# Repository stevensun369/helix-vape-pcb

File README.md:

# Helix Vape — Power Board

KiCad hardware design for the **Helix** temperature-control vape mod: a single-cell, USB-C powered board capable of delivering **1.0–10 V at up to 80 W** into a heating coil, with closed-loop current/voltage sensing and an ESP32-C6 running the [Helix-FW](https://github.com/stevensun369/helix-vape-fw) firmware.

The power stage is based on TI's **PMP20410** reference design, re-implemented and integrated with the MCU, sensing, and user-interface circuitry on a single board.

## Renders

| Front | Back |
|-------|------|
|  |  |

## Schematics

| Power & analog front-end | MCU & digital |
|--------------------------|---------------|
|  |  |

> Click either schematic to open the full-size SVG.

## How It Works

The board is a **digitally-controlled buck-boost regulator**. The MCU sets a target output via a DAC that injects into the regulator's feedback node, the ADC measures the actual coil current and voltage, and the firmware closes the loop with a PID controller. Because the regulator both bucks and boosts, it can hold a precise output regardless of where the battery sits in its discharge curve.

```
USB-C / Battery ──► LM5175 Buck-Boost ──► Q1–Q4 Power FETs ──► Coil
                         ▲                        │
                    MCP4726 DAC          RS1 / Rshunt sense
                         │                        │
                    ESP32-C6 ◄──────── ADS1015 ADC
```

## Key Components

| Ref | Part | Function |
|-----|------|----------|
| U1 | **LM5175PWP** | 4-switch synchronous buck-boost controller — the main 80 W power stage |
| U5 | **ESP32-C6-MINI-1U** | RISC-V MCU + Wi-Fi/BLE module; runs the control loop, UI, and safety logic |
| U4 | **ADS1015IDGS** | 12-bit I²C ADC — differential coil-current sensing plus single-ended Vout/Vbat |
| U3 | **MCP4726** | 12-bit I²C DAC — injects into the LM5175 feedback node to set output (inverse scaling) |
| Q1–Q4 | **BSC010NE2LSI** | 25 V, ~1 mΩ power MOSFETs — the buck-boost switching bridge |
| U2 | **LMR62014XMF** | Boost regulator for the auxiliary/gate-drive rail |
| U6 | **LP3986-30B3F** | 3.0 V LDO — clean rail for the MCU and analog parts |
| U8 | **USBLC6-2SC6** | USB-C data-line ESD / TVS protection |
| J1 | **USB-C Receptacle (16P)** | Charging and power input |
| RS1 / Rshunt1 | **2 mΩ / 10 mΩ shunts** | High-side and coil current sensing |
| L1 | **680 nH, 23 A** | Main power inductor (Chilisin) |
| BT1 | **1042 cell** | Battery connection |
| SW1 / SW2 | Push buttons | User input |

Full bill of materials with LCSC part numbers is in [`PRODUCTION_FILES/BOM-helix_vape.csv`](PRODUCTION_FILES/BOM-helix_vape.csv).

## Design Notes

- **Inverse DAC feedback:** higher DAC voltage produces *lower* output, so any logical fault or DAC reset biases the regulator toward a safe low-power idle (~1.0 V) rather than full power.
- **Shared I²C bus @ 400 kHz** ties together the ADC and DAC; the firmware arbitrates access to keep latency predictable under contention.
- **Differential current sensing** through the ADS1015 gives the firmware accurate, real-time coil current for PID power control and over-current safety.

## Files

| Path | Contents |
|------|----------|
| `helix_vape.kicad_pro` / `.kicad_sch` / `.kicad_pcb` | KiCad project, schematics, and board layout |
| `mcu.kicad_sch` | MCU subsheet |
| `PRODUCTION_FILES/` | Gerbers, BOM, and CPL (pick-and-place) for JLCPCB |
| `jlcpcb/` | JLCPCB fabrication / assembly outputs |
| `images/` | 3D renders and exported schematics |

## Manufacturing

Production files target **JLCPCB** assembly:

- `PRODUCTION_FILES/GERBER-helix_vape.zip` — fabrication Gerbers
- `PRODUCTION_FILES/BOM-helix_vape.csv` — bill of materials (LCSC part numbers)
- `PRODUCTION_FILES/CPL-helix_vape.csv` — component placement / pick-and-place

## Firmware

The board is driven by [Helix-FW](https://github.com/stevensun369/helix-vape-fw), an async Rust (Embassy) firmware with a host-testable safety and control logic core.

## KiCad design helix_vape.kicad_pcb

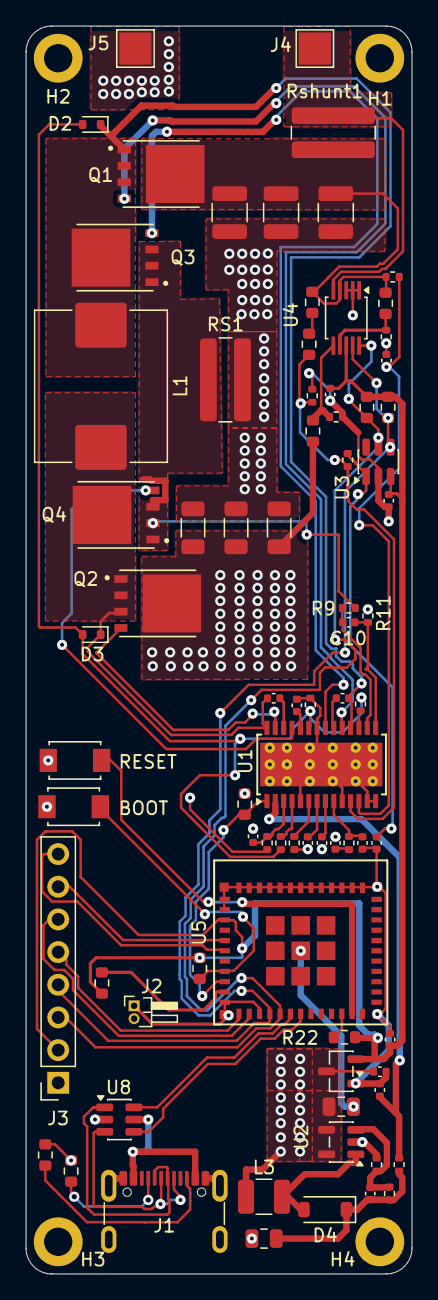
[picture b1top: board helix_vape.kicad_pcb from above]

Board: 2 copper layers, 30.0 x 97.0 mm, 83 parts (1 on the bottom side), 54 nets.

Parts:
BT1: 1042; BAT_1042
C1, C11: 100pF; C_0402_1005Metric
C2, C5, C9, C20, C22, C23: 0.1uF; C_0402_1005Metric
C3, C6: 0.22uF; C_0402_1005Metric
C4: 1uF; R_0402_1005Metric
C7: 0.047uF; C_0402_1005Metric
C8: 0.022uF; C_0402_1005Metric
C10: 220pF; C_0402_1005Metric
C13: 68pF; C_0402_1005Metric
C14: 560pF; C_0402_1005Metric
C24, C25: 2.2uF; C_0402_1005Metric
Cin1, Cin2, Cin3: 22uF; C_1206_3216Metric
Cin4: 4.7uF; C_0805_2012Metric
Cout1, Cout2, Cout3: 22uF; C_1210_3225Metric
Cout6: 4.7uF; C_0805_2012Metric
D2, D3: BASS516,115; D_SOD-523
D4: MBR0520LT1G; D_SOD-123
H1, H2, H3, H4: MountingHole_Pad; MountingHole_2.2mm_M2_DIN965_Pad
J1: USB-C Receptacle 16P; USB_C_Receptacle_GCT_USB4105-xx-A_16P_TopMnt_Horizontal
J2: Fire Button; PinHeader_1x02_P1.00mm_Horizontal
J3: OLED 0.96" Display; PinSocket_1x08_P2.54mm_Vertical
J4: 510 Power; TestPoint_Pad_2.5x2.5mm
J5: 510 Ground; TestPoint_Pad_2.5x2.5mm
L1: 680nH, 23A, 30A Isat; L_Chilisin_BMRF00101040
L3: 10uH; L_1210_3225Metric
Q1, Q2, Q3, Q4: BSC010NE2LSI; TRANS_BSC010NE2LSI
R1, R2, R3: 10; R_0402_1005Metric
R4, R6, R22, R23: 10k; R_0603_1608Metric
R5: 1.5k; R_0402_1005Metric
R7: 0; R_0402_1005Metric
R8: 47; R_0603_1608Metric
R9, R11: 100; R_0402_1005Metric
R10: 49.9k; R_0603_1608Metric
R13: 130k; R_0402_1005Metric
R14: 20k; R_0402_1005Metric
R15: 5.49k; R_0402_1005Metric
R16: 16.2k; R_0402_1005Metric
R18: 49.9k; R_0402_1005Metric
R19: 6.98k; R_0402_1005Metric
R20, R21: 5.1k; R_0603_1608Metric
R24, R25: 4.7k; R_0603_1608Metric
R26: 120k; R_0603_1608Metric
R27: 47k; R_0402_1005Metric
R28: 100k; R_0603_1608Metric
R29: 200k; R_0402_1005Metric
RS1: 2m; R_1225_3264Metric
Rshunt1: 10m; R_1225_3264Metric
SW1, SW2: SW_Push; SW_TS-1088-AR02016
U1: LM5175PWP; HTSSOP-28-1EP_4.4x9.7mm_P0.65mm_EP3.4x9.5mm_ThermalVias
U2: LMR62014XMF; SOT-23-5
U3: MCP4726; SOT-23-6
U4: ADS1015IDGS; TSSOP-10_3x3mm_P0.5mm
U5: ESP32-C6-MINI-1U; MOD53_ESP32-C6-MINI-1U_EXP
U6: LP3986-30B3F; SOT-23-3
U8: USBLC6-2SC6; SOT-23-6

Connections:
+3V3: C20.1, C23.1, C25.1, J3.2, R4.1, R22.1, R23.1, R24.1, R25.1, U3.3 (VDD), U4.8 (VDD), U5.3 (3V3), U6.2 (VO)
+5V: J1.A4 (VBUS), J1.A9 (VBUS), J1.B4 (VBUS), J1.B9 (VBUS), U8.5 (VBUS)
+10V: C14.1, Cout6.1, D4.1 (K), R2.1, R18.1
ADC_IN: R28.2, R29.1, U4.6 (AIN2)
ADC_OUT: R26.2, R27.1, U4.7 (AIN3)
ADC_SH_IN: Cout1.1, Cout2.1, Cout3.1, Q1.5_8, R1.1, R8.1, R26.1, Rshunt1.1, U4.4 (AIN0)
ADC_SH_OUT: J4.1 (Pin_1_1), Rshunt1.2, U4.5 (AIN1)
BIAS: C3.1, U1.24 (BIAS)
BOOT: SW1.1, U5.23 (IO9)
BOOT1: C9.2, U1.26 (BOOT1)
BOOT2: C5.2, U1.20 (BOOT2)
COMP: C8.1, R5.2, U1.9 (COMP)
CONV_FB: C22.1, R16.2, U3.1 (VOUT)
CS: C10.1, R9.1, U1.16 (CS)
CSG: C10.2, R11.1, U1.15 (CSG)
EN: R6.1, U1.1 (EN/UVLO), U5.9 (IO4)
FB: R10.2, R15.1, R16.1, U1.11 (FB)
FIRE: J2.2, R4.2, U5.10 (IO5)
GND: BT1.N, C1.2, C2.2, C3.2, C4.2, C6.2, C7.2, C8.2, C11.2, C13.2, C20.2, C22.2, C23.2, C24.2, C25.2, Cin1.2, Cin2.2, Cin3.2, Cin4.2, Cout1.2, Cout2.2, Cout3.2, Cout6.2, H1.1 (1_1), H2.1 (1_1), H3.1 (1_1), H4.1 (1_1), J1.A1 (GND), J1.A12 (GND), J1.B1 (GND), J1.B12 (GND), J1.SH (SHIELD), J2.1, J3.1, J5.1 (Pin_1_1), R6.2, R11.2, R13.2, R15.2, R19.2, R20.2, R21.2, R27.2, R29.2, RS1.2, SW1.2, SW2.2, U1.5 (DITH), U1.10 (AGND), U1.13 (ISNS(-)), U1.14 (ISNS(+)), U1.22 (PGND), U1.29 (PowerPAD), U2.2 (GND), U3.2 (VSS), U4.1 (ADDR), U4.2 (ALERT/RDY), U4.3 (GND), U5.1 (GND), U5.2 (GND), U5.11 (GND), U5.14 (GND), U5.36 (GND), U5.37 (GND), U5.38 (GND), U5.39 (GND), U5.40 (GND), U5.41 (GND), U5.42 (GND), U5.43 (GND), U5.44 (GND), U5.45 (GND), U5.46 (GND), U5.47 (GND), U5.48 (GND), U5.49 (GND), U5.50 (GND), U5.51 (GND), U5.52 (GND), U5.53 (GND), U6.1 (GND), U8.2 (GND)
HDRV1: Q2.4, U1.27 (HDRV1)
HDRV2: Q1.4, U1.19 (HDRV2)
K1: J3.5, U5.12 (IO0)
K2: J3.6, U5.13 (IO1)
K3: J3.7, U5.5 (IO2)
K4: J3.8, U5.6 (IO3)
LDRV1: Q4.4, U1.25 (LDRV1)
LDRV2: Q3.4, U1.21 (LDRV2)
MODE: R7.2, U1.4 (MODE)
unnamed: C7.1, R5.1
unnamed: D4.2 (A), L3.2, U2.1 (SW)
unnamed: J1.A5 (CC1), R20.1
unnamed: J1.B5 (CC2), R21.1
unnamed: J1.A6 (D+), J1.B6 (D+), U8.3 (I/O2)
unnamed: J1.A7 (D-), J1.B7 (D-), U8.1 (I/O1)
unnamed: R8.2, R10.1
unnamed: R14.2, U1.17 (PGOOD)
unnamed: C13.1, U1.7 (SLOPE)
unnamed: C14.2, R18.2, R19.1, U2.3 (FB)
unnamed: R22.2, U5.22 (IO8)
RESET: R23.2, SW2.1, U5.8 (EN)
SCL: J3.3, R25.2, U3.5 (SCL), U4.10 (SCL), U5.16 (IO7)
SDA: J3.4, R24.2, U3.4 (SDA), U4.9 (SDA), U5.15 (IO6)
SS: C6.1, U1.8 (SS)
SW1: C9.1, D3.1 (K), L1.1, Q2.1, Q2.2, Q2.3, Q4.5_8, U1.28 (SW1)
SW2: C5.1, D2.1 (K), L1.2, Q1.1, Q1.2, Q1.3, Q3.5_8, U1.18 (SW2)
SYNC: R13.1, U1.6 (RT/SYNC)
USB_D+: U5.18 (IO13), U8.4 (I/O2)
USB_D-: U5.17 (IO12), U8.6 (I/O1)
VCC: C4.1, D2.2 (A), D3.2 (A), R7.1, R14.1, U1.23 (VCC)
VIN: BT1.P, C24.1, Cin1.1, Cin2.1, Cin3.1, Cin4.1, L3.1, Q2.5_8, R3.1, R28.1, U2.4 (EN), U2.5 (VIN), U6.3 (VI)
VIN_IC: C2.1, R2.2, U1.2 (VIN)
VISNS: C11.1, R3.2, U1.3 (VISNS)
VOSNS: C1.1, R1.2, U1.12 (VOSNS)
VRS: Q3.1, Q3.2, Q3.3, Q4.1, Q4.2, Q4.3, R9.2, RS1.1

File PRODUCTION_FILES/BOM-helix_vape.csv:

Comment,Designator,Footprint,LCSC,Quantity
0,R7,R_0402_1005Metric,C881153,1
0.022uF,C8,C_0402_1005Metric,C107019,1
0.047uF,C7,C_0402_1005Metric,C285062,1
0.1uF,"C20,C22,C23",C_0402_1005Metric,C1525,3
0.1uF,"C2,C5,C9",C_0402_1005Metric,C85858,3
0.22uF,"C3,C6",C_0402_1005Metric,C696915,2
1.5k,R5,R_0402_1005Metric,C308014,1
10,"R1,R2,R3",R_0402_1005Metric,C176108,3
100,"R11,R9",R_0402_1005Metric,C82865,2
100k,R28,R_0603_1608Metric,C25803,1
100pF,"C1,C11",C_0402_1005Metric,C281751,2
1042,BT1,BAT_1042,C5249310,1
10k,"R22,R23,R4,R6",R_0603_1608Metric,C25804,4
10m,Rshunt1,R_1225_3264Metric,C304202,1
10uH,L3,L_1210_3225Metric,C22469024,1
120k,R26,R_0603_1608Metric,C25808,1
130k,R13,R_0402_1005Metric,C881362,1
16.2k,R16,R_0402_1005Metric,C27176,1
1uF,C4,R_0402_1005Metric,C29266,1
2.2uF,"C24,C25",C_0402_1005Metric,C12530,2
200k,R29,R_0402_1005Metric,C25811,1
20k,R14,R_0402_1005Metric,C5157652,1
220pF,C10,C_0402_1005Metric,C1530,1
22uF,"Cout1,Cout2,Cout3",C_1210_3225Metric,C2918511,3
22uF,"Cin1,Cin2,Cin3",C_1206_3216Metric,C87996,3
2m,RS1,R_1225_3264Metric,C7463342,1
4.7k,"R24,R25",R_0603_1608Metric,C23162,2
4.7uF,"Cin4,Cout6",C_0805_2012Metric,C107365,2
47,R8,R_0603_1608Metric,C23182,1
47k,R27,R_0402_1005Metric,C25819,1
49.9k,R10,R_0603_1608Metric,C23184,1
49.9k,R18,R_0402_1005Metric,C3008853,1
5.1k,"R20,R21",R_0603_1608Metric,C14677,2
5.49k,R15,R_0402_1005Metric,C407675,1
560pF,C14,C_0402_1005Metric,C107029,1
6.98k,R19,R_0402_1005Metric,C852901,1
"680nH, 23A, 30A Isat",L1,L_Chilisin_BMRF00101040,C2921223,1
68pF,C13,C_0402_1005Metric,C76977,1
ADS1015IDGS,U4,TSSOP-10_3x3mm_P0.5mm,C193969,1
"BASS516,115","D2,D3",D_SOD-523,C10037,2
BSC010NE2LSI,"Q1,Q2,Q3,Q4",TRANS_BSC010NE2LSI,C534282,4
ESP32-C6-MINI-1U,U5,MOD53_ESP32-C6-MINI-1U_EXP,C20627095,1
LM5175PWP,U1,HTSSOP-28-1EP_4.4x9.7mm_P0.65mm_EP3.4x9.5mm_ThermalVias,C113356,1
LMR62014XMF,U2,SOT-23-5,C468235,1
LP3986-30B3F,U6,SOT-23-3,C387690,1
MBR0520LT1G,D4,D_SOD-123,C23848,1
MCP4726,U3,SOT-23-6,C191581,1
SW_Push,"SW1,SW2",SW_TS-1088-AR02016,C720477,2
USB-C Receptacle 16P,J1,USB_C_Receptacle_GCT_USB4105-xx-A_16P_TopMnt_Horizontal,C2765186,1
USBLC6-2SC6,U8,SOT-23-6,C7519,1

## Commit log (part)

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2026-05-28 had some problems
2026-06-15 added a README with images
